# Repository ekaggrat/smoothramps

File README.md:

View this project on [CADLAB.io](https://cadlab.io/node/991). 

# smoothramps

This board is meant to be used with the standard ramps board as a replacement for the arduino mega. The purpose is to use smoothieware
on a ramps board as a alternative to the smoothieboard. This board lacks some of the bells and wistles of the smoothieboard like digipots 
but still has the basic functions to run a 3d printer.

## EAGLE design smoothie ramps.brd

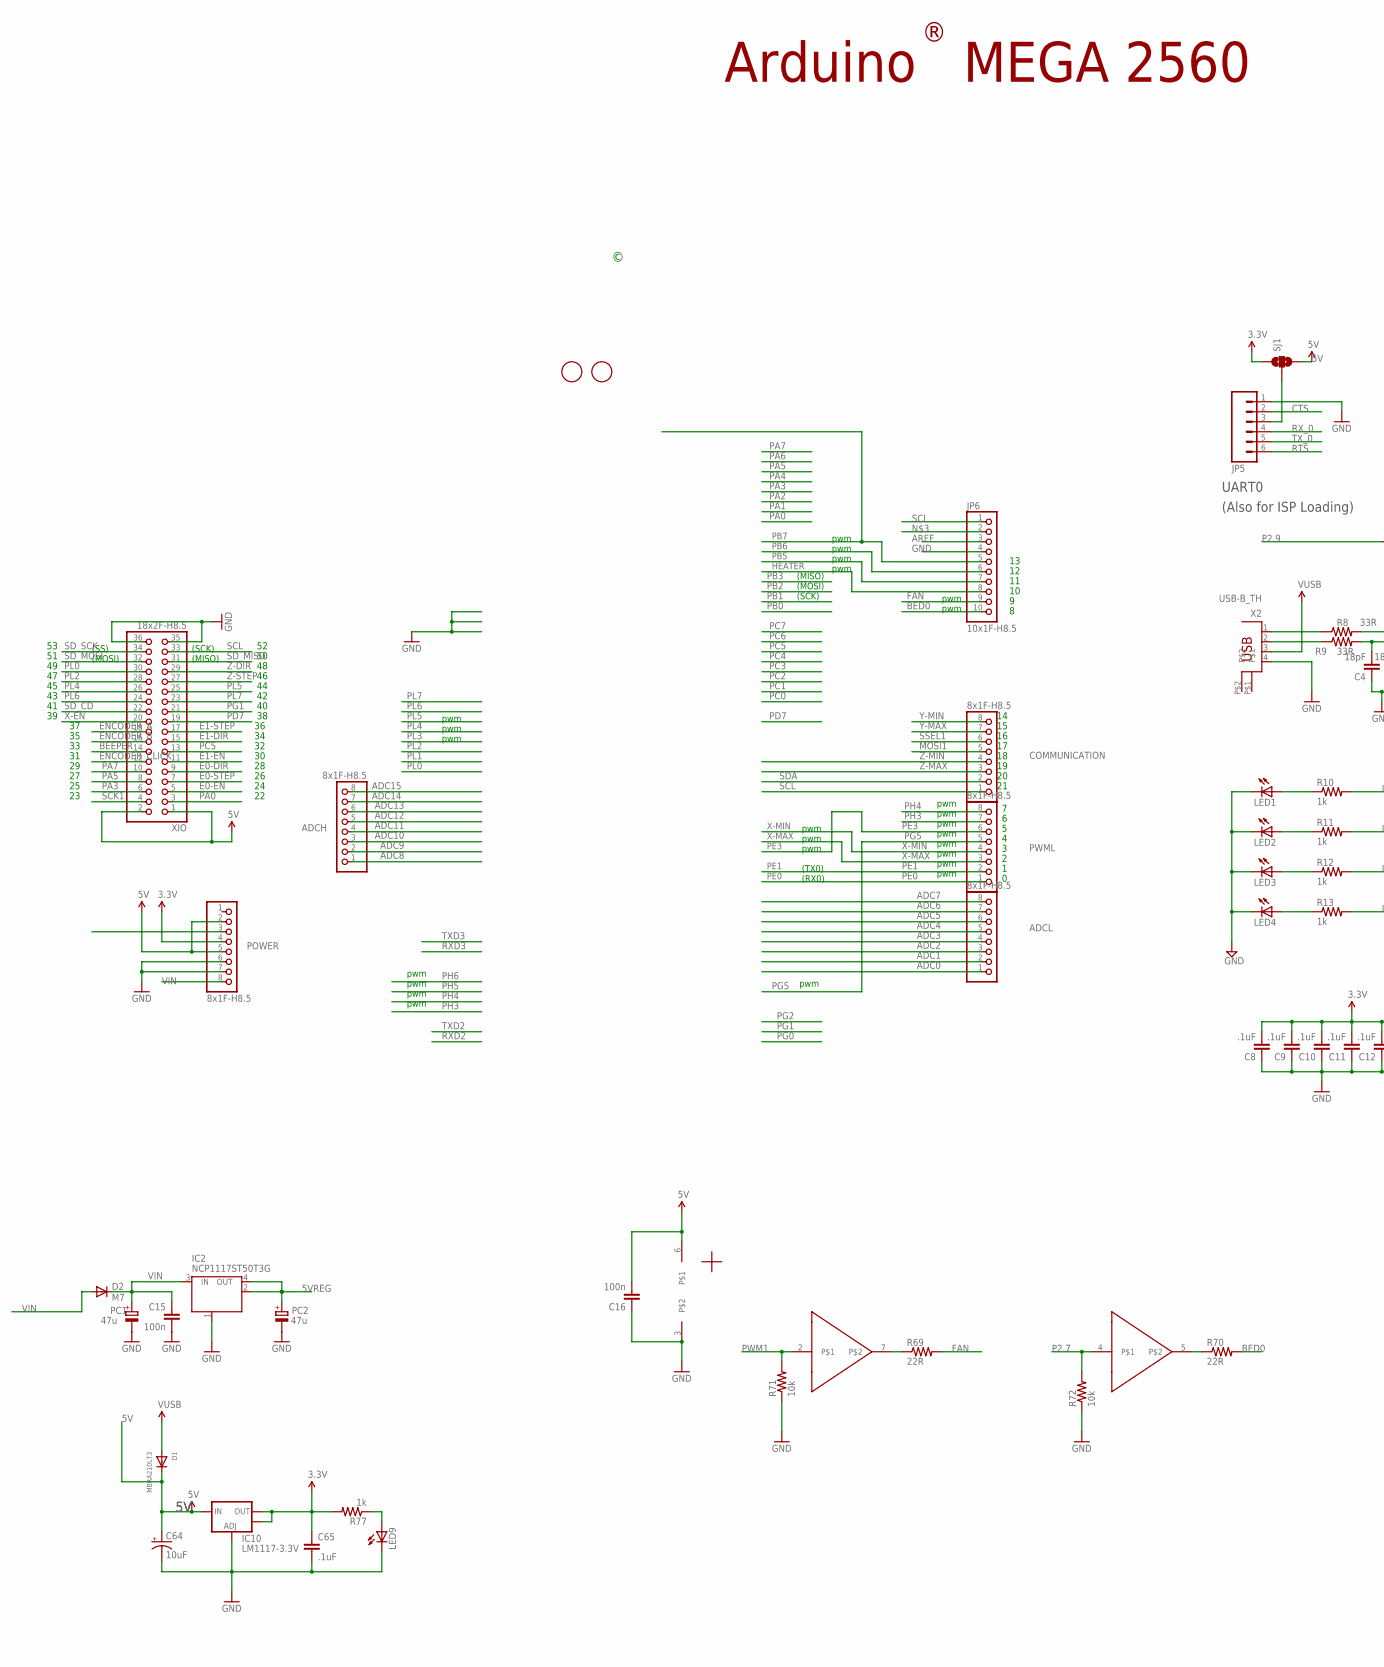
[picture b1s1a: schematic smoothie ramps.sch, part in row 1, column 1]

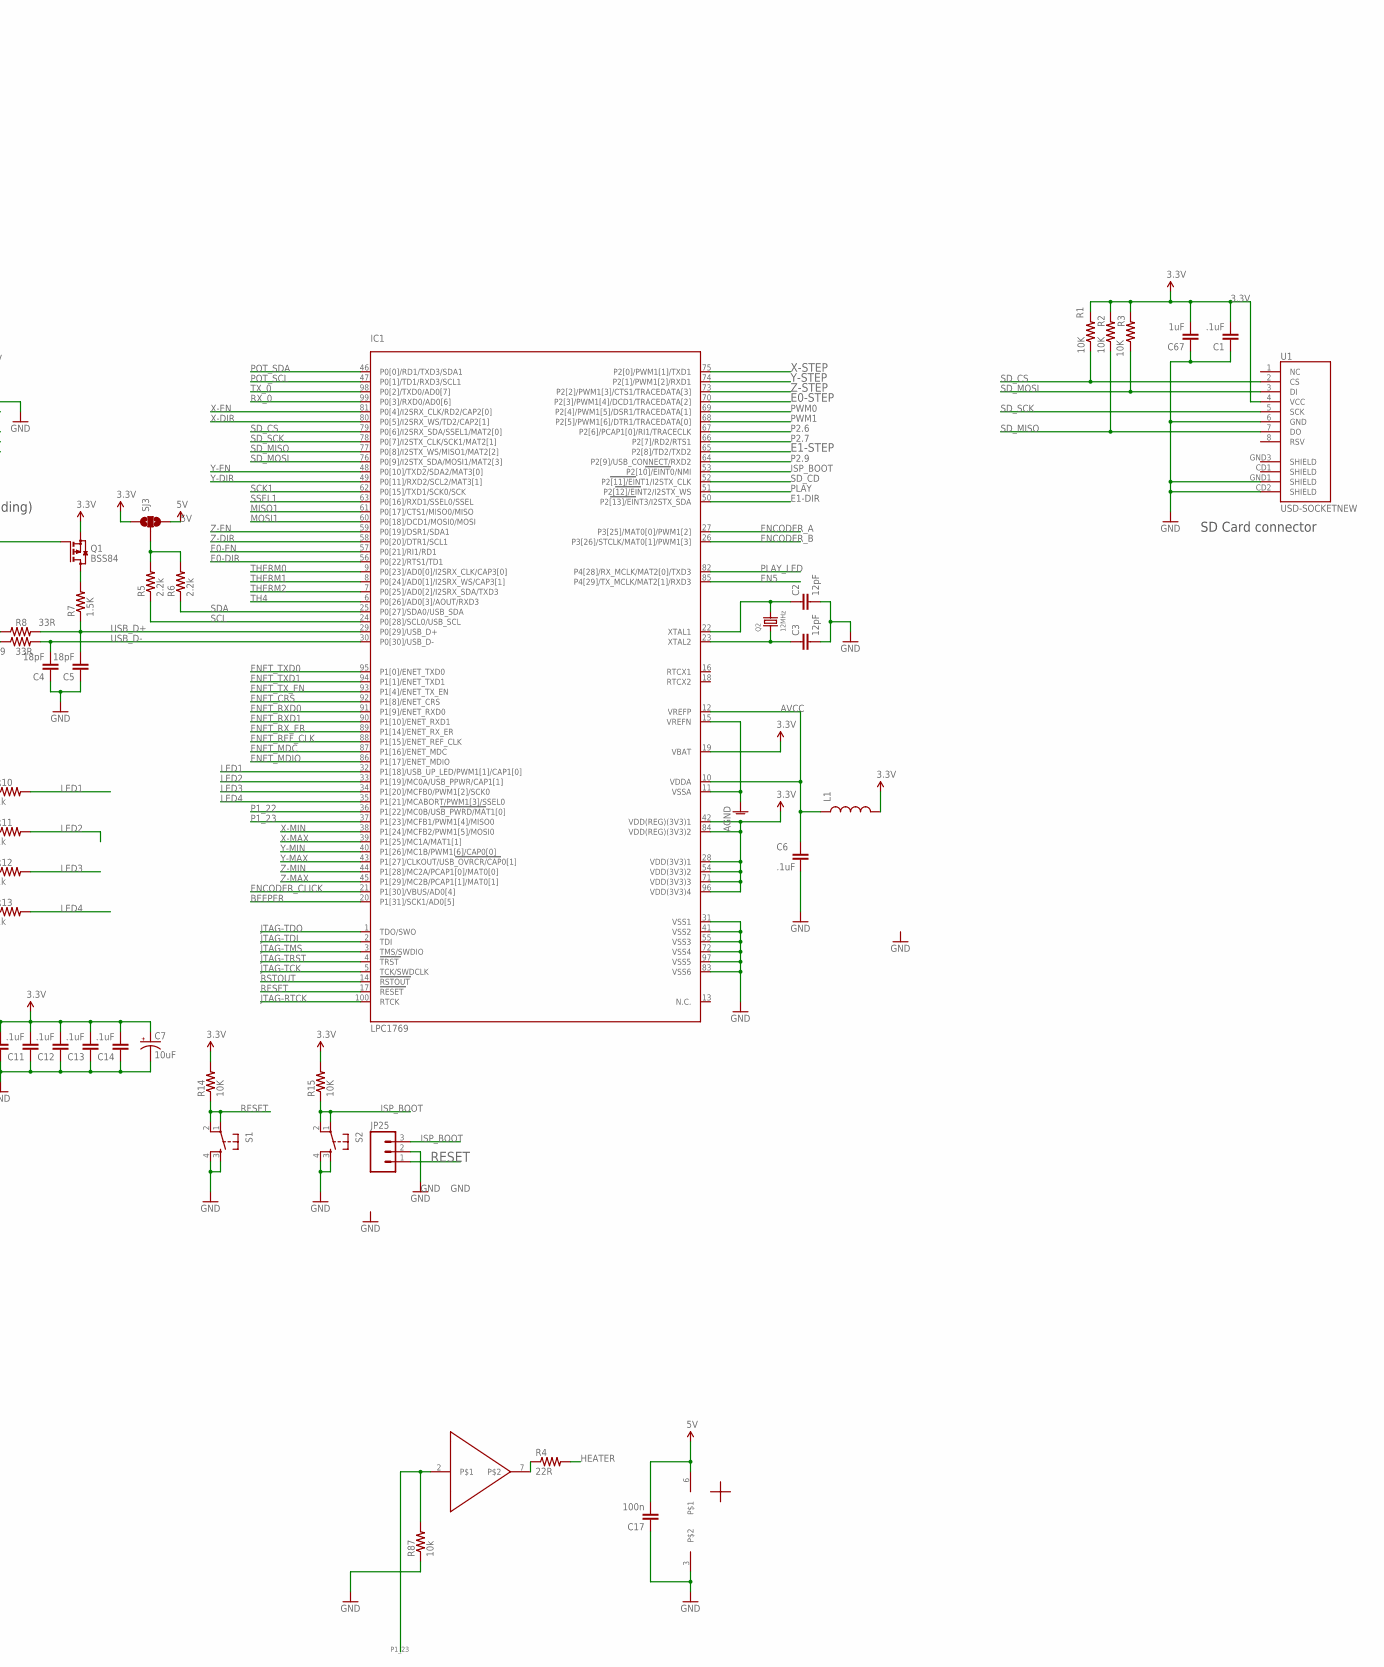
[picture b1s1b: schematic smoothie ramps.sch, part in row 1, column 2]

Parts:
ADCH: 8x1F-H8.5; 1X08
ADCL: 8x1F-H8.5; 1X08
C1, C6, C8, C9, C10, C11, C12, C13, C14, C65: .1uF; C0603
C2, C3: 12pF; C0603
C4, C5: 18pF; C0603
C7, C64: 10uF; EIA3216
C15: 100n; C0603-ROUND
C16, C17: 100n; C0603
C67: 1uF; C0805
COMMUNICATION: 8x1F-H8.5; 1X08
D1: MBRA210LT3; SMADIODE
D2: M7; SMB
FD2, FD3: FIDUCIALMOUNT; FIDUCIA-MOUNT
IC1: LPC1769; LQFP100
IC2: NCP1117ST50T3G; SOT223
IC10: LM1117-3.3V; SOT223
IC14, IC15: TC4427; SOIC8
JP5: M06POLAR; MOLEX-1X6
JP6: 10x1F-H8.5; 1X10
JP25: M03PTH; 1X03
L1: INDUCTOR0603; 0603
LED1, LED2, LED3, LED4, LED9: LEDCHIP-LED0805; CHIP-LED0805
PC1, PC2: 47u; PANASONIC_D
POWER: 8x1F-H8.5; 1X08
PWML: 8x1F-H8.5; 1X08
Q1: BSS84; SOT23
Q2: 12MHz; CRYSTAL_3.2X2.5
R1, R2, R3, R14, R15: 10K; R0603
R4, R69, R70: 22R; R0603
R5, R6: 2.2k; R0603
R7: 1.5K; R0603
R8, R9: 33R; R0603
R10, R11, R12, R13, R77: 1k; R0603
R71, R72, R87: 10k; R0603
S1, S2: TAC_SWITCHSMD; TACTILE_SWITCH_SMD
SJ1, SJ3: SOLDERJUMPER_2WAYS; SJ_3
U1: USD-SOCKETNEW; MICRO-SD-SOCKET-PP
X2: USB-B_TH; PN61729
XIO: 18x2F-H8.5; 2X18

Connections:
3.3V: C1.2, C7.A (+), C8.2, C9.2, C10.2, C11.2, C12.2, C13.2, C14.2, C65.1, C67.2, IC1.19 (VBAT), IC1.28 (VDD(3V3)1), IC1.42 (VDD(REG)(3V3)1), IC1.54 (VDD(3V3)2), IC1.71 (VDD(3V3)3), IC1.84 (VDD(REG)(3V3)2), IC1.96 (VDD(3V3)4), IC10.2 (OUT), IC10.4 (OUT), L1.2, POWER.4, Q1.2 (S), R1.2, R2.2, R3.2, R14.2, R15.2, R77.2, SJ1.1, SJ3.1, U1.4 (VCC)
5V: C16.2, C17.2, C64.A (+), D1.C, IC10.3 (IN), IC14.6, IC15.6, POWER.2, POWER.5, SJ1.3, SJ3.3, XIO.1, XIO.2
5VREG: IC2.2 (OUT), IC2.4 (OUT), PC2.+
ADC0: ADCL.1
ADC1: ADCL.2
ADC2: ADCL.3
ADC3: ADCL.4
ADC4: ADCL.5
ADC5: ADCL.6
ADC6: ADCL.7
ADC7: ADCL.8
ADC8: ADCH.1
ADC9: ADCH.2
ADC10: ADCH.3
ADC11: ADCH.4
ADC12: ADCH.5
ADC13: ADCH.6
ADC14: ADCH.7
ADC15: ADCH.8
AGND: IC1.11 (VSSA), IC1.15 (VREFN)
AREF: JP6.3
AVCC: C6.1, IC1.10 (VDDA), IC1.12 (VREFP), L1.1
BED0: JP6.10, R70.2
BEEPER: IC1.20 (P1[31]/SCK1/AD0[5]), XIO.14
CTS: JP5.2
E0-DIR: IC1.56 (P0[22]/RTS1/TD1), XIO.9
E0-EN: IC1.57 (P0[21]/RI1/RD1), XIO.5
E0-STEP: IC1.70 (P2[3]/PWM1[4]/DCD1/TRACEDATA[2]), XIO.7
E1-DIR: IC1.50 (P2[13]/EINT3/I2STX_SDA), XIO.15
E1-EN: XIO.11
E1-STEP: IC1.65 (P2[8]/TD2/TXD2), XIO.17
EN5: IC1.85 (P4[29]/TX_MCLK/MAT2[1]/RXD3)
ENCODER_A: IC1.27 (P3[25]/MAT0[0]/PWM1[2]), XIO.18
ENCODER_B: IC1.26 (P3[26]/STCLK/MAT0[1]/PWM1[3]), XIO.16
ENCODER_CLICK: IC1.21 (P1[30]/VBUS/AD0[4]), XIO.12
ENET_CRS: IC1.92 (P1[8]/ENET_CRS)
ENET_MDC: IC1.87 (P1[16]/ENET_MDC)
ENET_MDIO: IC1.86 (P1[17]/ENET_MDIO)
ENET_REF_CLK: IC1.88 (P1[15]/ENET_REF_CLK)
ENET_RXD0: IC1.91 (P1[9]/ENET_RXD0)
ENET_RXD1: IC1.90 (P1[10]/ENET_RXD1)
ENET_RX_ER: IC1.89 (P1[14]/ENET_RX_ER)
ENET_TXD0: IC1.95 (P1[0]/ENET_TXD0)
ENET_TXD1: IC1.94 (P1[1]/ENET_TXD1)
ENET_TX_EN: IC1.93 (P1[4]/ENET_TX_EN)
FAN: JP6.9, R69.2
GND: C1.1, C2.2, C3.2, C4.1, C5.1, C6.2, C7.C (-), C8.1, C9.1, C10.1, C11.1, C12.1, C13.1, C14.1, C15.2, C16.1, C17.1, C64.C (-), C65.2, C67.1, IC1.31 (VSS1), IC1.41 (VSS2), IC1.55 (VSS3), IC1.72 (VSS4), IC1.83 (VSS6), IC1.97 (VSS5), IC2.1 (GND/ADJ), IC10.1 (ADJ), IC14.3, IC15.3, JP5.1, JP6.4, JP25.2, LED1.C, LED2.C, LED3.C, LED4.C, LED9.C, PC1.-, PC2.-, POWER.6, POWER.7, R71.1, R72.1, R87.1, S1.3, S1.4, S2.3, S2.4, U1.6 (GND), U1.CD2 (SHIELD), U1.GND1 (SHIELD), X2.4, XIO.35, XIO.36
HEATER: JP6.8, R4.2
ISP_BOOT: IC1.53 (P2[10]/EINT0/NMI), JP25.3, R15.1, S2.1, S2.2
JTAG-RTCK: IC1.100 (RTCK)
JTAG-TCK: IC1.5 (TCK/SWDCLK)
JTAG-TDI: IC1.2 (TDI)
JTAG-TDO: IC1.1 (TDO/SWO)
JTAG-TMS: IC1.3 (TMS/SWDIO)
JTAG-TRST: IC1.4 (TRST)
LED1: IC1.32 (P1[18]/USB_UP_LED/PWM1[1]/CAP1[0]), R10.2
LED2: IC1.33 (P1[19]/MC0A/USB_PPWR/CAP1[1]), R11.2
LED3: IC1.34 (P1[20]/MCFB0/PWM1[2]/SCK0), R12.2
LED4: IC1.35 (P1[21]/MCABORT/PWM1[3]/SSEL0), R13.2
MISO1: IC1.61 (P0[17]/CTS1/MISO0/MISO)
MOSI1: COMMUNICATION.5, IC1.60 (P0[18]/DCD1/MOSI0/MOSI)
unnamed: C2.1, IC1.22 (XTAL1), Q2.2
unnamed: C3.1, IC1.23 (XTAL2), Q2.1
unnamed: IC15.7, R4.1
unnamed: IC14.7, R69.1
unnamed: IC14.5, R70.1
unnamed: JP5.3, SJ1.2
unnamed: Q1.3 (D), R7.2
unnamed: R8.1, X2.1
unnamed: R9.1, X2.2
unnamed: LED9.A, R77.1
unnamed: LED4.A, R13.1
unnamed: LED3.A, R12.1
unnamed: LED2.A, R11.1
unnamed: LED1.A, R10.1
unnamed: R5.2, R6.2, SJ3.2
P1_22: IC1.36 (P1[22]/MC0B/USB_PWRD/MAT1[0])
P1_23: IC1.37 (P1[23]/MCFB1/PWM1[4]/MISO0), IC15.2, R87.2
P2.6: IC1.67 (P2[6]/PCAP1[0]/RI1/TRACECLK)
P2.7: IC1.66 (P2[7]/RD2/RTS1), IC14.4, R72.2
P2.9: IC1.64 (P2[9]/USB_CONNECT/RXD2), Q1.1 (G)
PA0: XIO.3
PA3: XIO.6
PA5: XIO.8
PA7: XIO.10
PB5: JP6.7
PB6: JP6.6
PB7: JP6.5
PC5: XIO.13
PD7: XIO.19
PE0: PWML.1
PE1: PWML.2
PE3: PWML.6
PG1: XIO.21
PG5: PWML.5
PH3: PWML.7
PH4: PWML.8
PL0: XIO.30
PL2: XIO.28
PL4: XIO.26
PL5: XIO.25
PL6: XIO.24
PL7: XIO.23
PLAY: IC1.51 (P2[12]/EINT2/I2STX_WS)
PLAY_LED: IC1.82 (P4[28]/RX_MCLK/MAT2[0]/TXD3)
POT_SCL: IC1.47 (P0[1]/TD1/RXD3/SCL1)
POT_SDA: IC1.46 (P0[0]/RD1/TXD3/SDA1)
PWM0: IC1.69 (P2[4]/PWM1[5]/DSR1/TRACEDATA[1])
PWM1: IC1.68 (P2[5]/PWM1[6]/DTR1/TRACEDATA[0]), IC14.2, R71.2
RESET: IC1.17 (RESET), JP25.1, POWER.3, R14.1, S1.1, S1.2
RSTOUT: IC1.14 (RSTOUT)
RTS: JP5.6
RX_0: IC1.99 (P0[3]/RXD0/AD0[6]), JP5.4
SCK1: IC1.62 (P0[15]/TXD1/SCK0/SCK), XIO.4
SCL: COMMUNICATION.1, IC1.24 (P0[28]/SCL0/USB_SCL), JP6.1, R5.1, XIO.33
SDA: COMMUNICATION.2, IC1.25 (P0[27]/SDA0/USB_SDA), R6.1
SD_CD: IC1.52 (P2[11]/EINT1/I2STX_CLK), XIO.22
SD_CS: IC1.79 (P0[6]/I2SRX_SDA/SSEL1/MAT2[0]), R1.1, U1.2 (CS)
SD_MISO: IC1.77 (P0[8]/I2STX_WS/MISO1/MAT2[2]), R2.1, U1.7 (DO), XIO.31
SD_MOSI: IC1.76 (P0[9]/I2STX_SDA/MOSI1/MAT2[3]), R3.1, U1.3 (DI), XIO.32
SD_SCK: IC1.78 (P0[7]/I2STX_CLK/SCK1/MAT2[1]), U1.5 (SCK), XIO.34
SSEL1: COMMUNICATION.6, IC1.63 (P0[16]/RXD1/SSEL0/SSEL)
TH4: IC1.6 (P0[26]/AD0[3]/AOUT/RXD3)
THERM0: IC1.9 (P0[23]/AD0[0]/I2SRX_CLK/CAP3[0])
THERM1: IC1.8 (P0[24]/AD0[1]/I2SRX_WS/CAP3[1])
THERM2: IC1.7 (P0[25]/AD0[2]/I2SRX_SDA/TXD3)
TX_0: IC1.98 (P0[2]/TXD0/AD0[7]), JP5.5
USB_D+: C5.2, IC1.29 (P0[29]/USB_D+), R7.1, R8.2
USB_D-: C4.2, IC1.30 (P0[30]/USB_D-), R9.2
VIN: C15.1, D2.A, D2.C, IC2.3 (IN), PC1.+, POWER.8
VUSB: D1.A, X2.3
X-DIR: IC1.80 (P0[5]/I2SRX_WS/TD2/CAP2[1])
X-EN: IC1.81 (P0[4]/I2SRX_CLK/RD2/CAP2[0]), XIO.20
X-MAX: IC1.39 (P1[25]/MC1A/MAT1[1]), PWML.3
X-MIN: IC1.38 (P1[24]/MCFB2/PWM1[5]/MOSI0), PWML.4
X-STEP: IC1.75 (P2[0]/PWM1[1]/TXD1)
Y-DIR: IC1.49 (P0[11]/RXD2/SCL2/MAT3[1])
Y-EN: IC1.48 (P0[10]/TXD2/SDA2/MAT3[0])
Y-MAX: COMMUNICATION.7, IC1.43 (P1[27]/CLKOUT/USB_OVRCR/CAP0[1])
Y-MIN: COMMUNICATION.8, IC1.40 (P1[26]/MC1B/PWM1[6]/CAP0[0])
Y-STEP: IC1.74 (P2[1]/PWM1[2]/RXD1)
Z-DIR: IC1.58 (P0[20]/DTR1/SCL1), XIO.29
Z-EN: IC1.59 (P0[19]/DSR1/SDA1)
Z-MAX: COMMUNICATION.3, IC1.45 (P1[29]/MC2B/PCAP1[1]/MAT0[1])
Z-MIN: COMMUNICATION.4, IC1.44 (P1[28]/MC2A/PCAP1[0]/MAT0[0])
Z-STEP: IC1.73 (P2[2]/PWM1[3]/CTS1/TRACEDATA[3]), XIO.27

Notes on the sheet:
Arduino MEGA 2560
pwm
(TX0)
(RX0)
(MISO)
(SCK)
(MOSI)
(SS)
SD Card connector
UART0
(Also for ISP Loading)

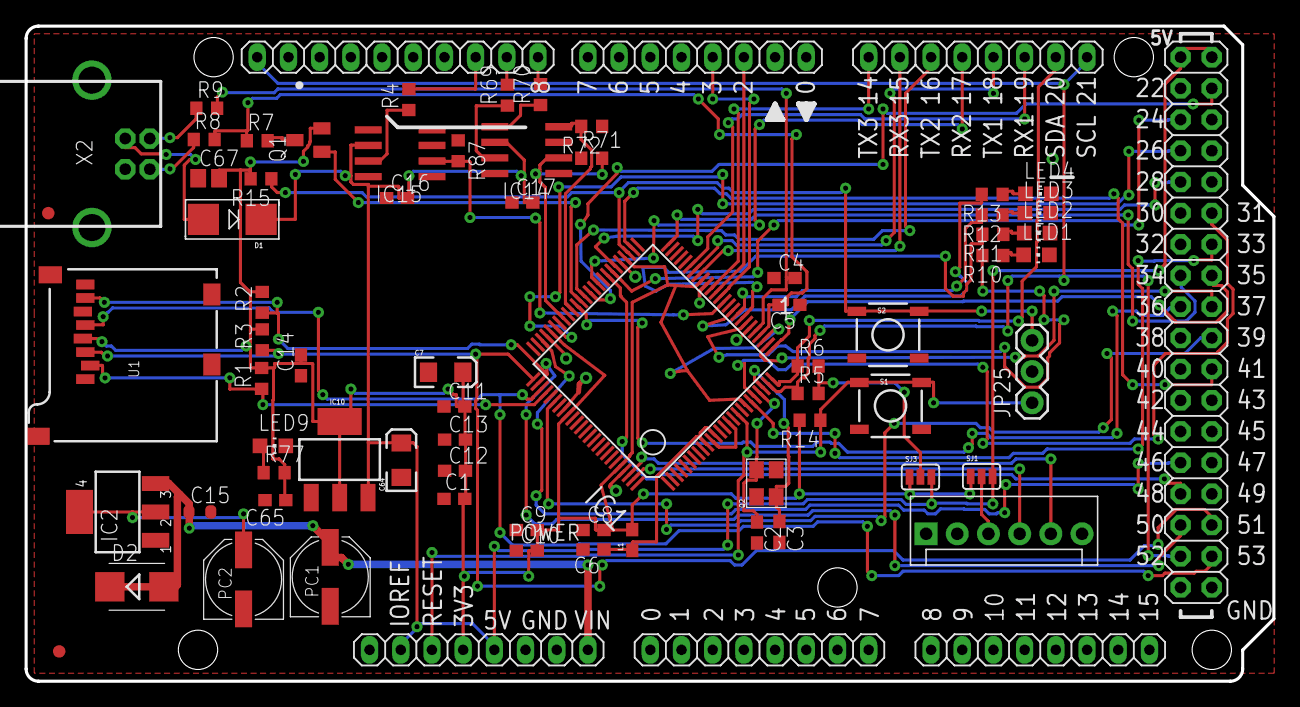
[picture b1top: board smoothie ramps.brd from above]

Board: 2 copper layers, 101.6 x 53.3 mm, 75 parts (0 on the bottom side), 68 nets.

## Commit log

2018-05-07 Backlink to CADLAB.io has been added.

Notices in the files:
parts and their libraries:
SparkFun-Connectors: Licensing: CC v3.0 Share-Alike You are welcome to use this library for commercial purposes.
